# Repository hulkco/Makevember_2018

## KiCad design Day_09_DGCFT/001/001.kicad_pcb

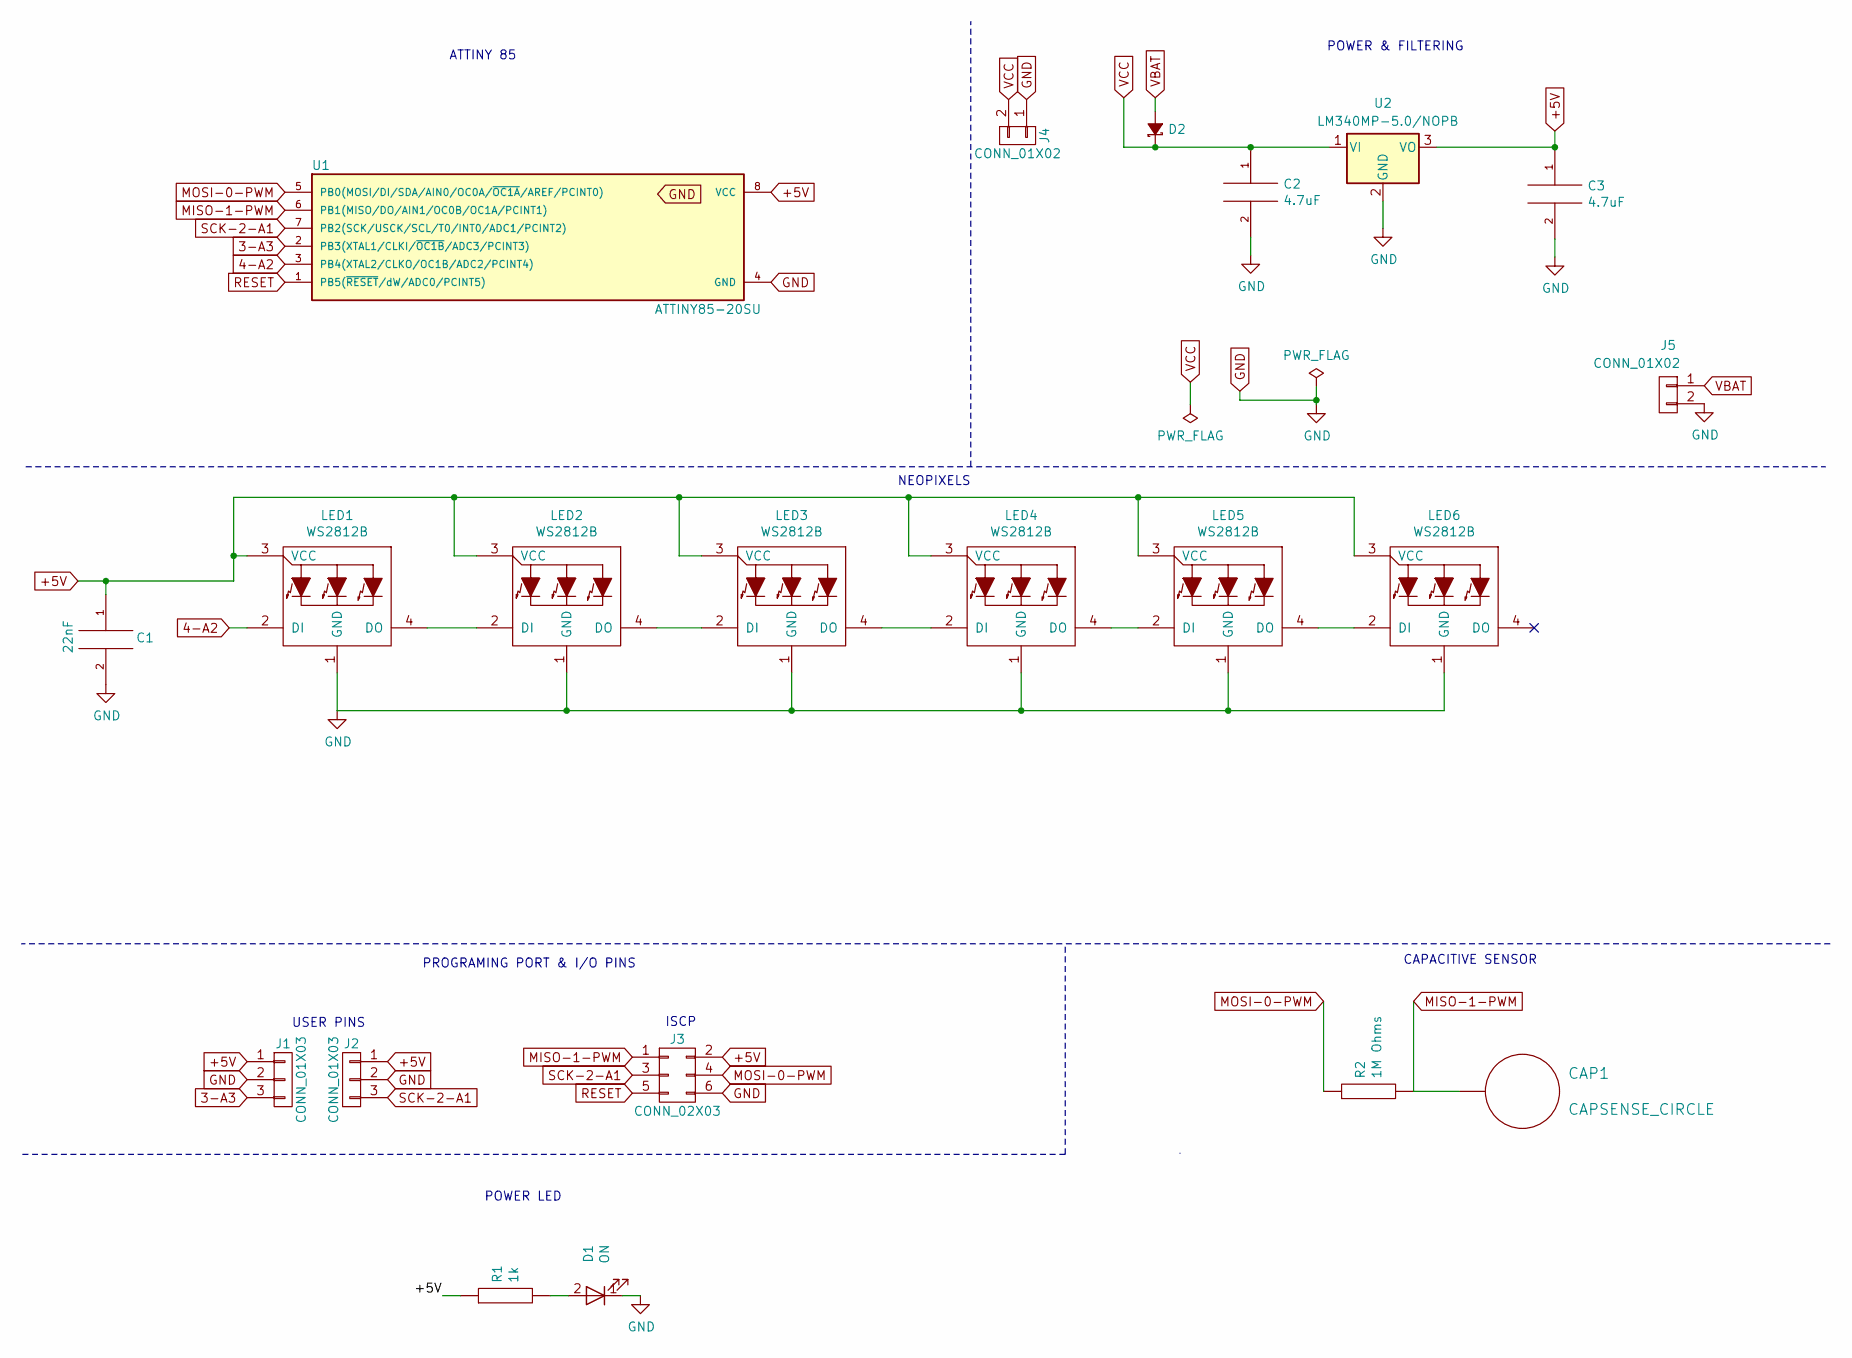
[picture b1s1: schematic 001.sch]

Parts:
C1: 22nF; C_1206_HandSoldering
C2, C3: 4.7uF; C_1206_HandSoldering
CAP1: CAPSENSE_CIRCLE; CAPSENSE-CIRCLE2-D10MM
D1: ON; LED_1206_HandSoldering
D2: MBRA140; DIODE-SMA
J1, J2: CONN_01X03; Pin_Header_Straight_1x03_Pitch2.54mm_SMD_Pin1Left
J3: CONN_02X03; Pin_Header_Straight_2x03_Pitch2.54mm_SMD
J4: CONN_01X02; Pin_Header_Straight_1x02_Pitch2.54mm_SMD_Pin1Left
J5: CONN_01X02; Molex_PicoBlade_53261-0271_02x1.25mm_Angled
LED1, LED2, LED3, LED4, LED5, LED6: WS2812B
R1: 1k; R_1206_HandSoldering
R2: 1M Ohms; R_1206_HandSoldering
U1: ATTINY85-20SU; SOIJ-8_5.3x5.3mm_Pitch1.27mm
U2: LM340MP-5.0/NOPB; SOT-223-3Lead_TabPin2

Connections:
3-A3: J1.3, U1.2 (PB3(XTAL1/CLKI/~OC1B~/ADC3/PCINT3))
4-A2: LED1.2 (DI), U1.3 (PB4(XTAL2/CLKO/OC1B/ADC2/PCINT4))
+5V: C1.1, C3.1, J1.1, J2.1, J3.2, LED1.3 (VCC), LED2.3 (VCC), LED3.3 (VCC), LED4.3 (VCC), LED5.3 (VCC), LED6.3 (VCC), R1.1, U1.8 (VCC), U2.3 (VO)
GND: C1.2, C2.2, C3.2, D1.1 (K), J1.2, J2.2, J3.6, J4.1, J5.2, LED1.1 (GND), LED2.1 (GND), LED3.1 (GND), LED4.1 (GND), LED5.1 (GND), LED6.1 (GND), U1.4 (GND), U2.2 (GND)
MISO-1-PWM: CAP1.1, J3.1, R2.2, U1.6 (PB1(MISO/DO/AIN1/OC0B/OC1A/PCINT1))
MOSI-0-PWM: J3.4, R2.1, U1.5 (PB0(MOSI/DI/SDA/AIN0/OC0A/~OC1A~/AREF/P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)
unnamed: D1.2 (A), R1.2
unnamed: LED1.4 (DO), LED2.2 (DI)
unnamed: LED2.4 (DO), LED3.2 (DI)
unnamed: LED3.4 (DO), LED4.2 (DI)
unnamed: LED4.4 (DO), LED5.2 (DI)
unnamed: LED5.4 (DO), LED6.2 (DI)
RESET: J3.5, U1.1 (PB5(~RESET~/dW/ADC0/PCINT5))
SCK-2-A1: J2.3, J3.3, U1.7 (PB2(SCK/USCK/SCL/T0/INT0/ADC1/PCINT2))
VBAT: D2.2 (A), J5.1
VCC: C2.1, D2.1 (K), J4.2, U2.1 (VI)

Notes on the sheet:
POWER & FILTERING
ATTINY 85
NEOPIXELS
PROGRAMING PORT & I/O PINS
CAPACITIVE SENSOR
ISCP
USER PINS
POWER LED

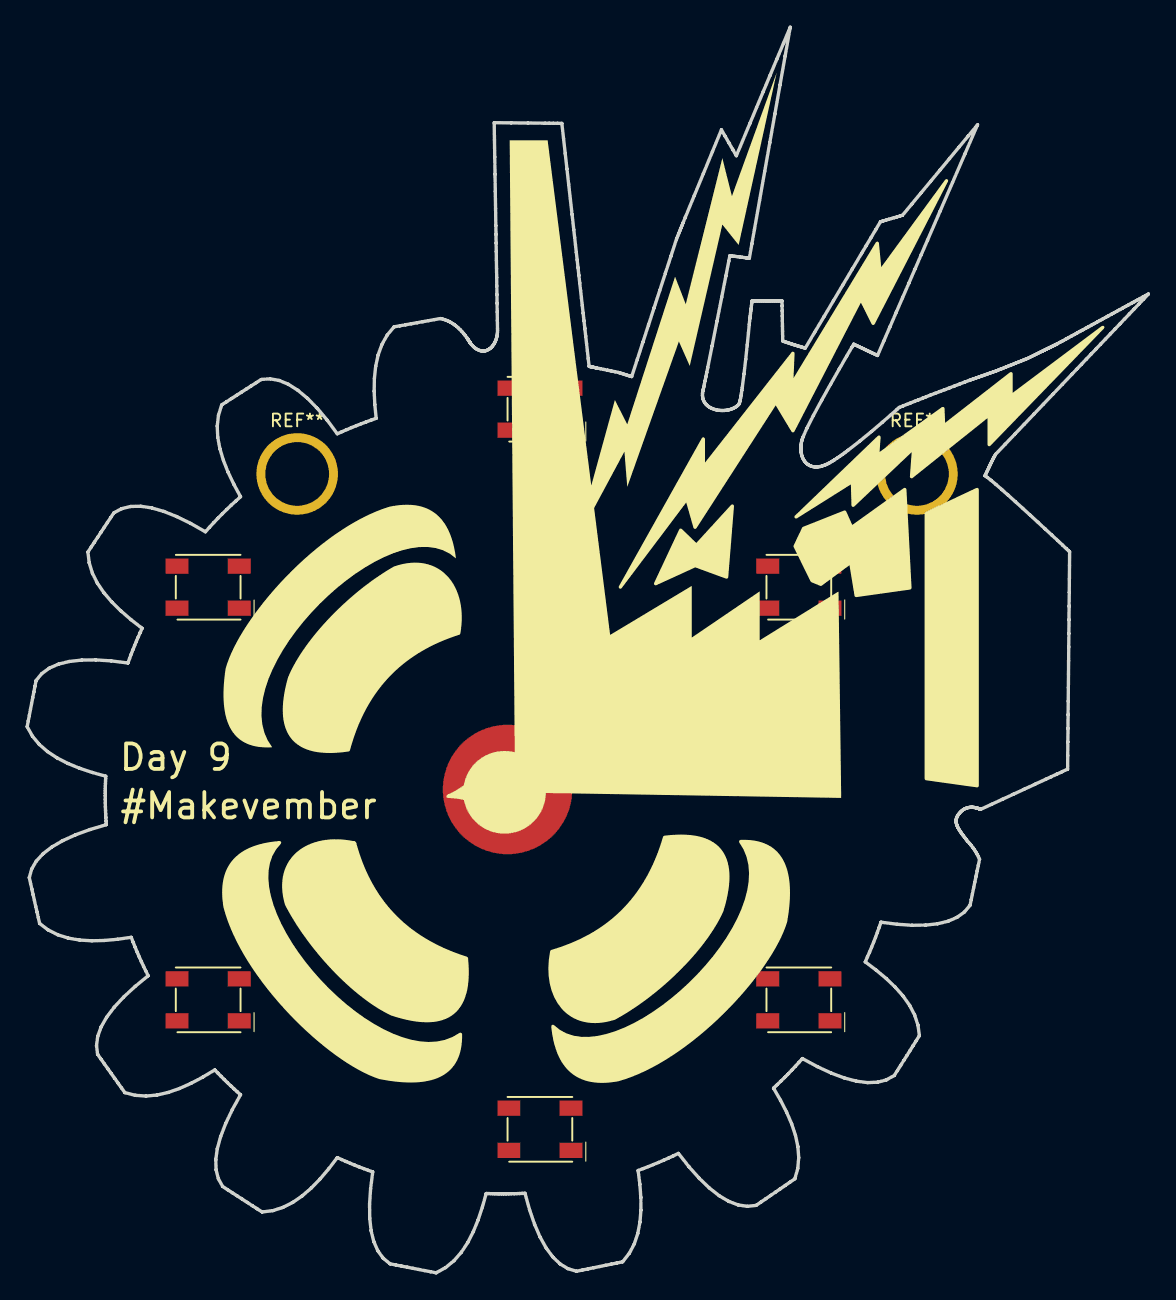
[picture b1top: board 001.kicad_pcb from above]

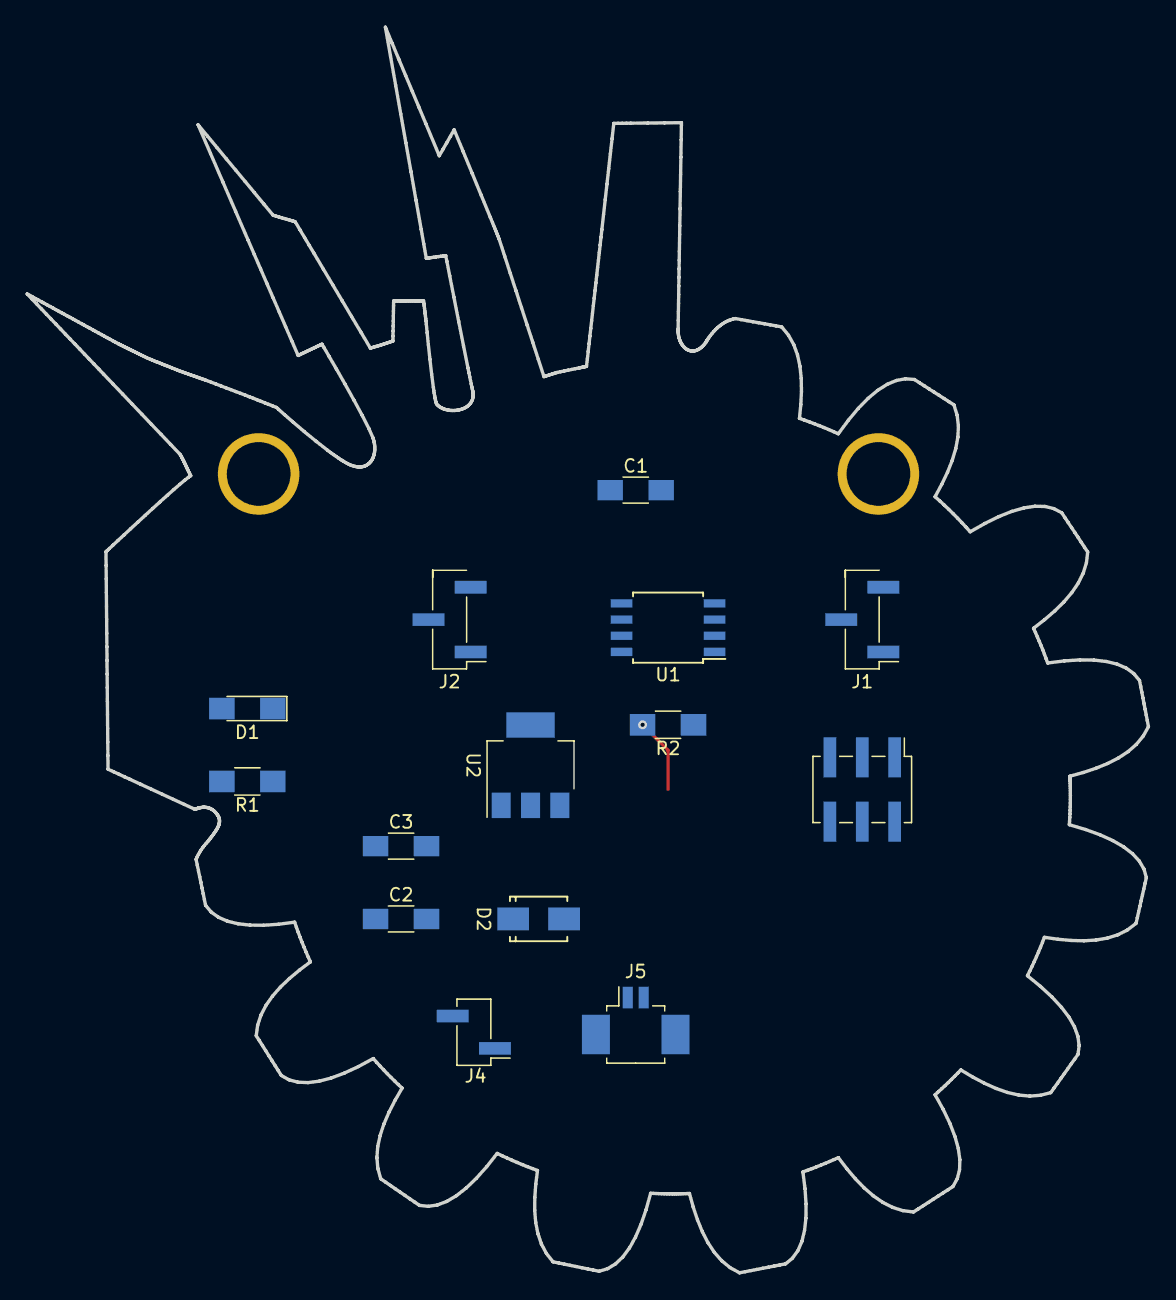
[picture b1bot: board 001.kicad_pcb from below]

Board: 2 copper layers, 88.0 x 97.8 mm, 22 parts (14 on the bottom side), 16 nets.

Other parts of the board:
svg2mod: G***; Dgcft.All.01

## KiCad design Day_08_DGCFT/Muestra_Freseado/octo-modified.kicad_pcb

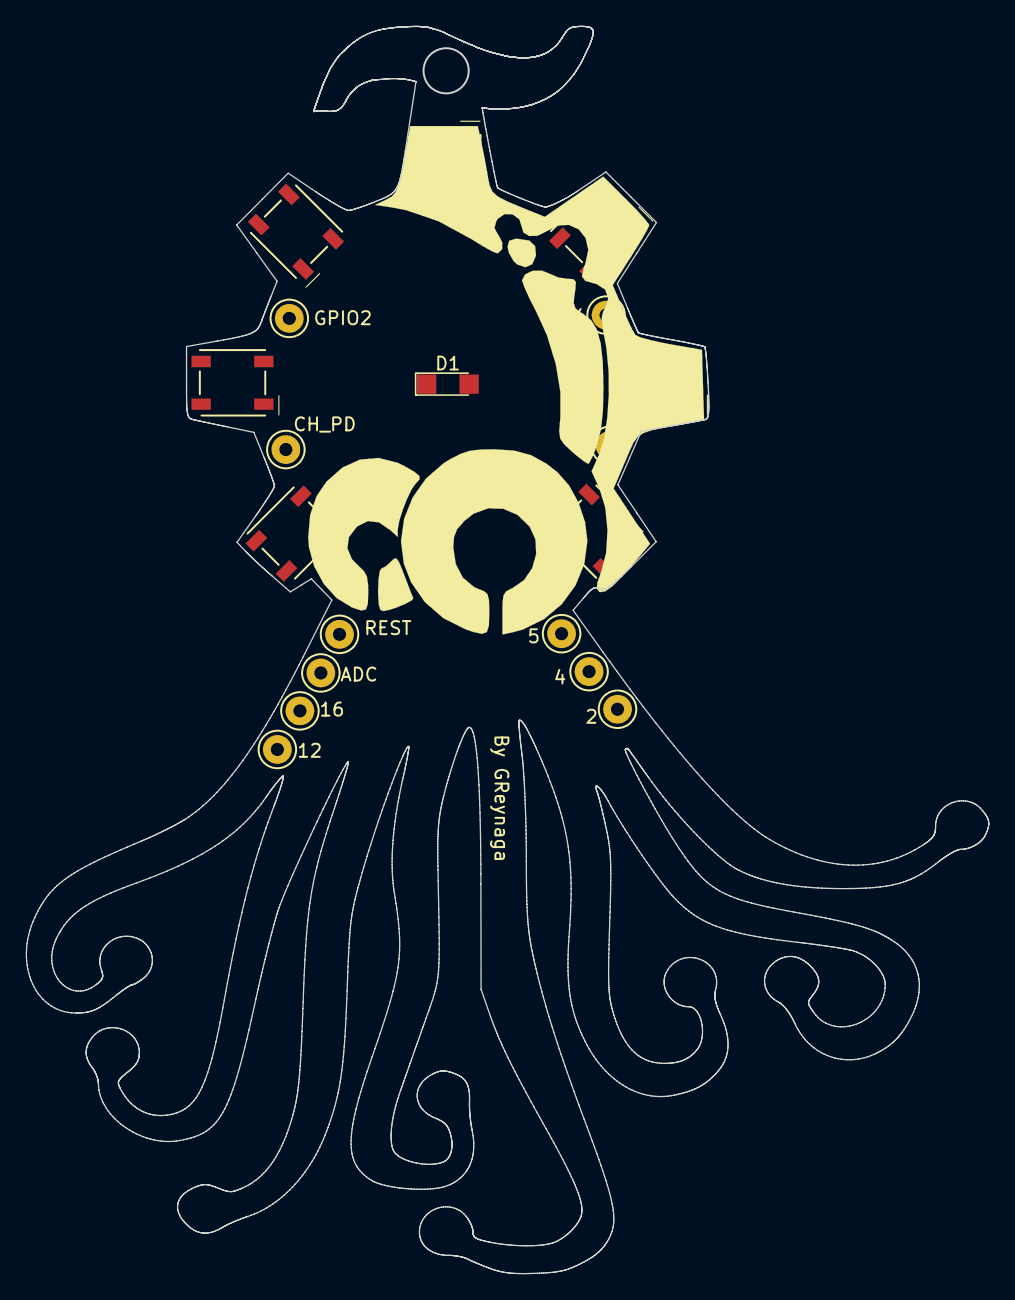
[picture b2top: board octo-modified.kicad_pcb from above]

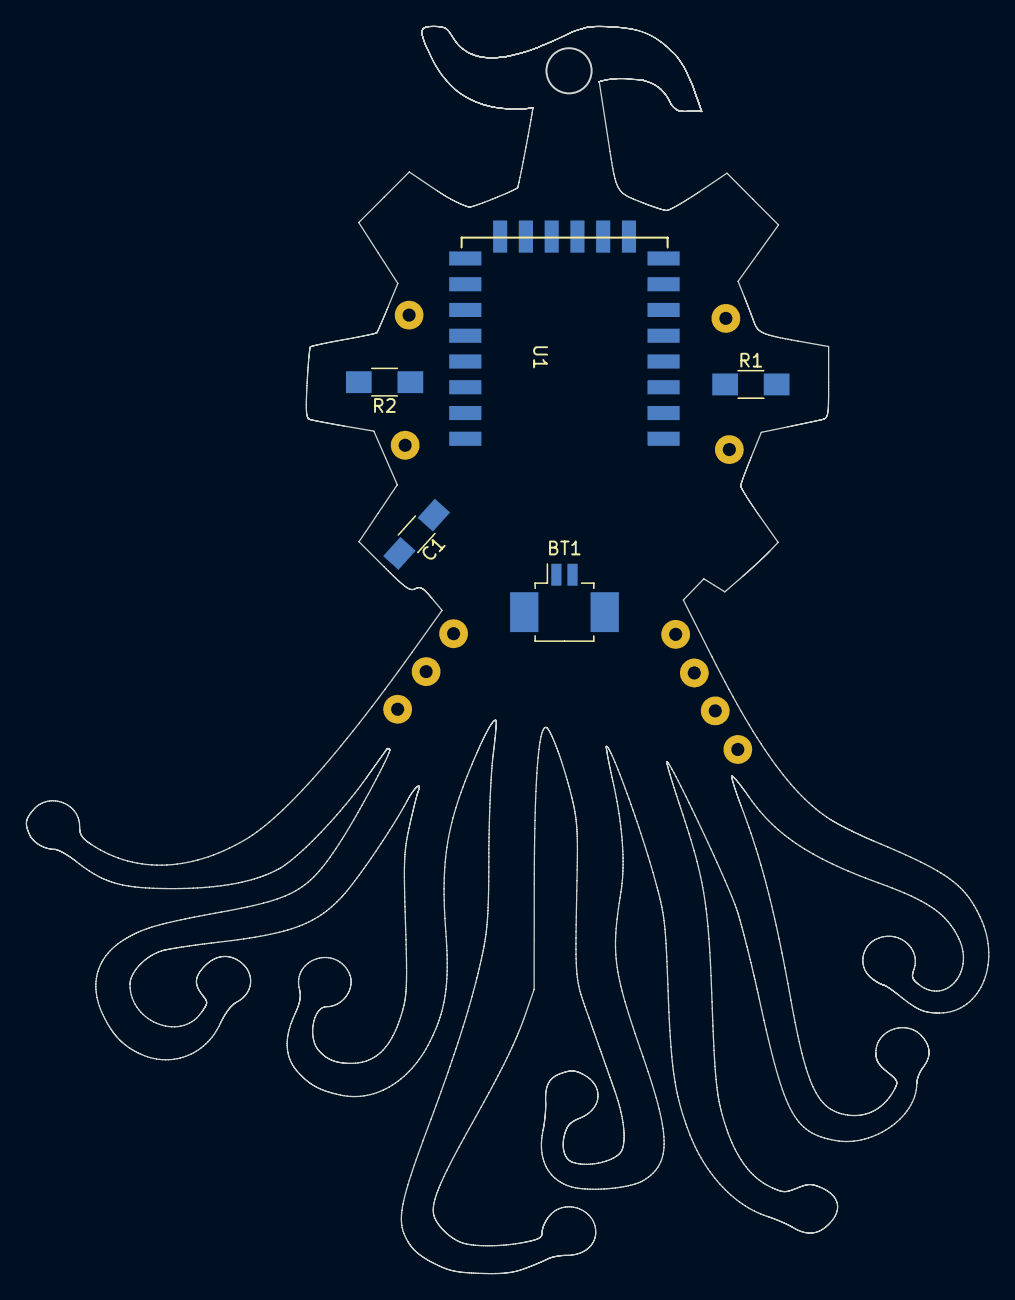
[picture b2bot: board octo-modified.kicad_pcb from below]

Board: 2 copper layers, 74.7 x 96.8 mm, 24 parts (5 on the bottom side), 21 nets, no tracks yet.

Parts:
BT1: LIPO; Molex_PicoBlade_53261-0271_02x1.25mm_Angled
C1: 100uF; C_1206_HandSoldering
D1: LED; LED_1206
J1, J2, J3, J4, J6, J8, J9, J10, J11, J12, J13: TEST_1P; CONN-HEADER-STRAIGHT-P2.54MM-1x01
LED1, LED2, LED3, LED4, LED5, LED6, LED7: LED-RGB-WS2812B-4SMD; LED-RGB-5050-SMD
R1: 1k; R_1206_HandSoldering
R2: 10k; R_1206_HandSoldering
U1: ESP-12E; ESP-12E_SMD

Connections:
ADC: J3.1, U1.2
CH_PD: J1.1, U1.3
GND: BT1.2, C1.2, LED1.1, LED2.1, LED3.1, LED4.1, LED5.1, LED6.1, LED7.1, R2.2, U1.9
GPIO0: J12.1, R1.2, U1.12
GPIO2: J13.1, U1.11
GPIO4: J11.1, U1.13
GPIO5: J10.1, R2.1, U1.14
GPIO12: J6.1, U1.6
GPIO16: J4.1, U1.4
NEOP: LED1.2, U1.5
unnamed: D1.1, R1.1
unnamed: LED1.4, LED2.2
unnamed: LED2.4, LED3.2
unnamed: LED3.4, LED4.2
unnamed: LED4.4, LED7.2
unnamed: LED5.2, LED6.4
unnamed: LED6.2, LED7.4
REST: J2.1, U1.1
RXD: J9.1, U1.15
TXD: J8.1, U1.16
VCC: BT1.1, C1.1, D1.2, LED1.3, LED2.3, LED3.3, LED4.3, LED5.3, LED6.3, LED7.3, U1.8

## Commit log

2018-11-08 Upload projets from Playa Computer
2018-11-08 Day 8 update
2022-02-03 Add new images
